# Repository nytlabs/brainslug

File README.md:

brainslug
=========

Brainslug is the internal name for a wearable we're experimenting with - this is the board that powers it. It combines an RFduino (ARM Cortex + BLE stack) and some MOSFET drivers to actuate high-current peripherals (heat pad, super-bright LED, peltier junction, etc).

Eagle board files for a small RFD22301 shield

This board allows an RFD22301 unit to address a dual-channel N-MOSFET IC on pins 0 and 1.

BOM:

(1) MOSFET IC http://www.digikey.com/product-detail/en/FDS6911/FDS6911CT-ND/1197695

(1) 3V3 regulator https://www.sparkfun.com/products/11253

(1) RFD22301 http://www.semiconductorstore.com/cart/pc/viewPrd.asp?idproduct=48872

(1) 10uF 0805 cap https://www.sparkfun.com/products/11244 (not strictly necessary, but wise)

...the board is laid out to use SMD JST connectors (https://www.sparkfun.com/products/8612) for battery and two loads, but you can also solder your own connectiors

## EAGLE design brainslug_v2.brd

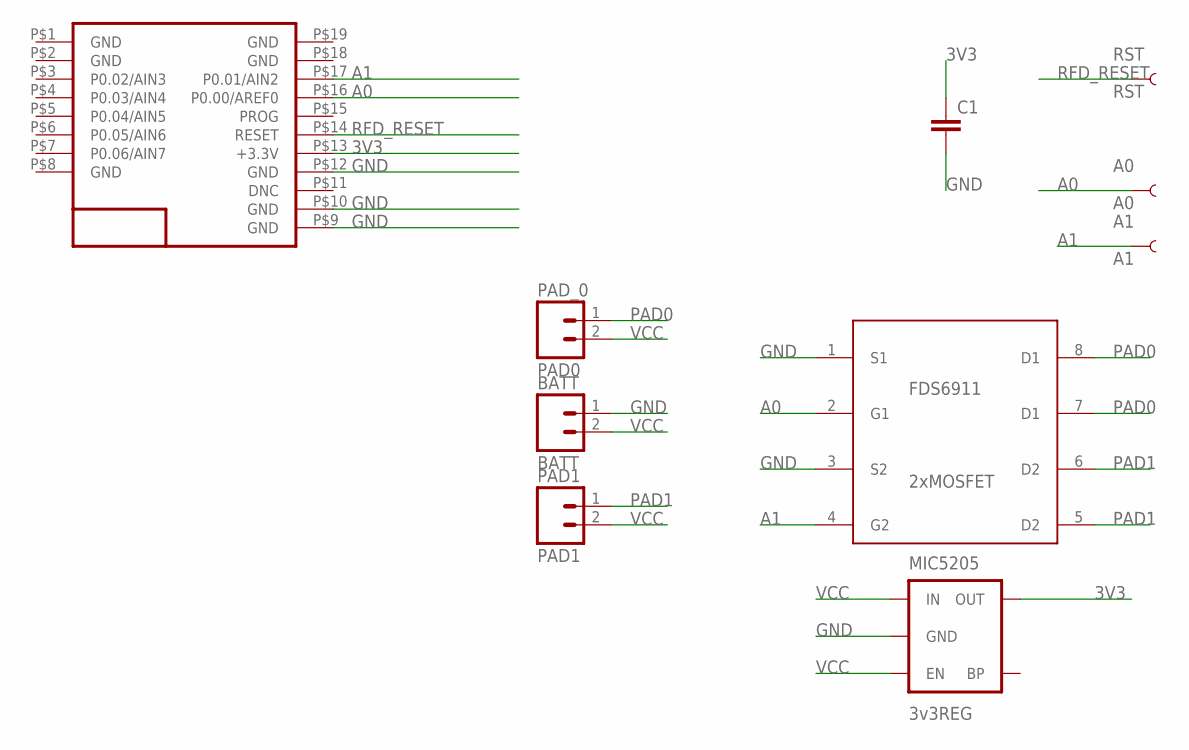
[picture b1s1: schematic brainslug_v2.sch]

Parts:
A0: A0; PAD.03X.03
A1: A1; PAD.03X.03
BATT: BATT; JST-2-SMD
C1: CAP; C3216
FDS6911: 2xMOSFET; SO8
MIC5205: 3v3REG; SOT23-5
PAD1: PAD1; JST-2-SMD
PAD_0: PAD0; JST-2-SMD
RST: RST; PAD.03X.03
U$1: RFD22301; RFD21733

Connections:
3V3: C1.1, MIC5205.5 (OUT), U$1.P$13 (+3.3V)
A0: A0.P$1, FDS6911.2 (G1), U$1.P$16 (P0.00/AREF0)
A1: A1.P$1, FDS6911.4 (G2), U$1.P$17 (P0.01/AIN2)
GND: BATT.1 (2), C1.2, FDS6911.1 (S1), FDS6911.3 (S2), MIC5205.2 (GND), U$1.P$9 (GND), U$1.P$10 (GND), U$1.P$12 (GND)
PAD0: FDS6911.7 (D1), FDS6911.8 (D1), PAD_0.1 (2)
PAD1: FDS6911.5 (D2), FDS6911.6 (D2), PAD1.1 (2)
RFD_RESET: RST.P$1, U$1.P$14 (RESET)
VCC: BATT.2 (1), MIC5205.1 (IN), MIC5205.3 (EN), PAD1.2 (1), PAD_0.2 (1)

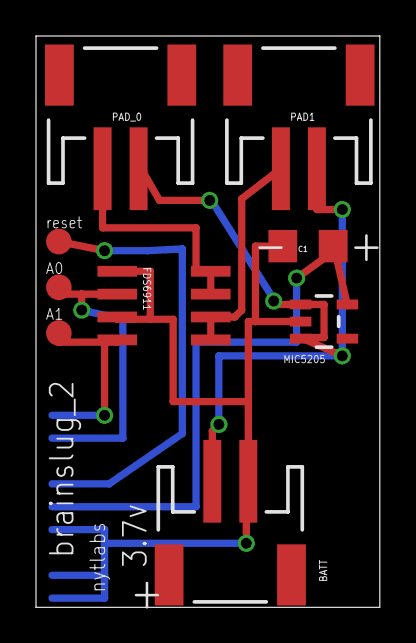
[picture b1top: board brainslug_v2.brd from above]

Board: 2 copper layers, 19.1 x 31.7 mm, 10 parts (1 on the bottom side), 8 nets.

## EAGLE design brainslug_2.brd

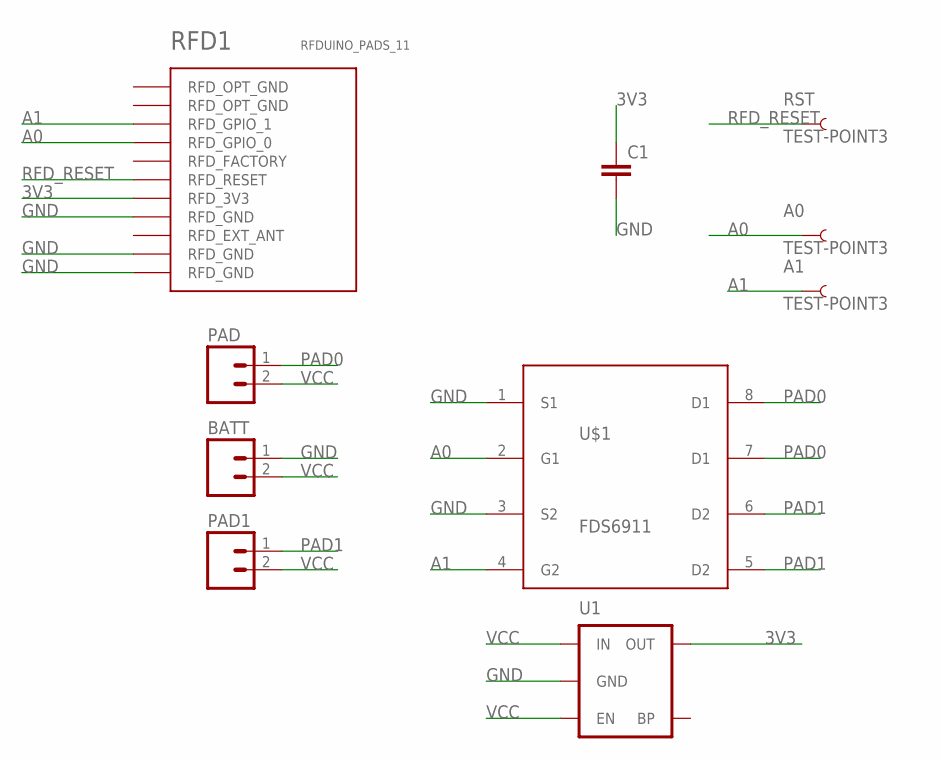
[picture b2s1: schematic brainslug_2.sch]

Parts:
A0, A1: TEST-POINT3; PAD.03X.03
BATT: M02-JST-2MM-SMT; JST-2-SMD
C1: CAP; C3216
PAD, PAD1: M02-JST-2MM-SMT; JST-2-SMD
RFD1: RFDUINO_PADS_11; RFDUINO_PADS
RST: TEST-POINT3; PAD.03X.03
U1: MIC52053.3V; SOT23-5
U$1: FDS6911; SO8

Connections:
3V3: C1.1, RFD1.RFD_3V3, U1.5 (OUT)
A0: A0.P$1, RFD1.RFD_GPIO_0, U$1.2 (G1)
A1: A1.P$1, RFD1.RFD_GPIO_1, U$1.4 (G2)
GND: BATT.1 (2), C1.2, RFD1.RFD_GND@0 (RFD_GND), RFD1.RFD_GND@1 (RFD_GND), RFD1.RFD_GND@2 (RFD_GND), U1.2 (GND), U$1.1 (S1), U$1.3 (S2)
PAD0: PAD.1 (2), U$1.7 (D1), U$1.8 (D1)
PAD1: PAD1.1 (2), U$1.5 (D2), U$1.6 (D2)
RFD_RESET: RFD1.RFD_RESET, RST.P$1
VCC: BATT.2 (1), PAD.2 (1), PAD1.2 (1), U1.1 (IN), U1.3 (EN)

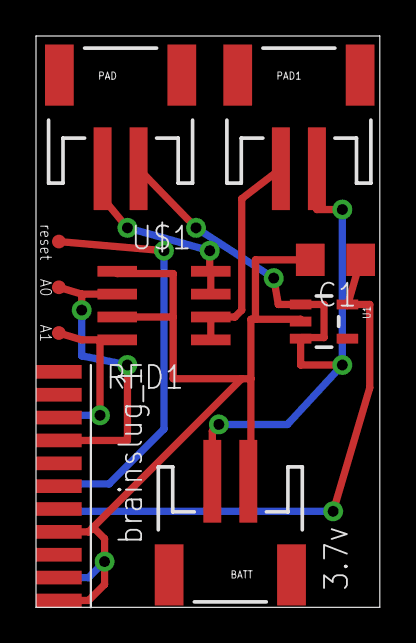
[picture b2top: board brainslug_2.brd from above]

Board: 2 copper layers, 19.1 x 31.7 mm, 10 parts (0 on the bottom side), 8 nets.

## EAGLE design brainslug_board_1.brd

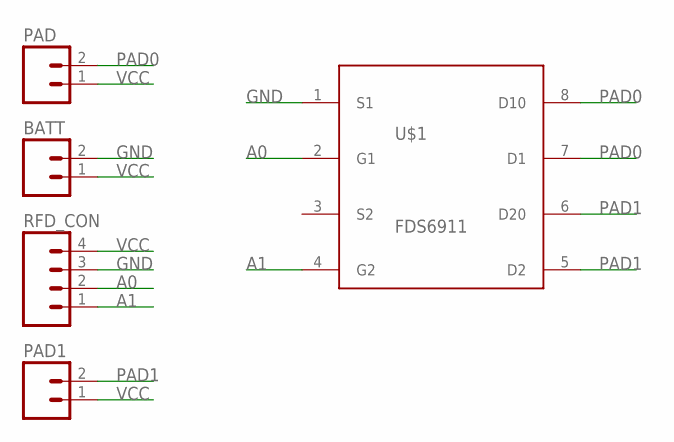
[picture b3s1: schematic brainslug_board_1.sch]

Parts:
BATT: M02PTH; 1X02
PAD, PAD1: M02PTH; 1X02
RFD_CON: M04PTH; 1X04
U$1: FDS6911; SO8

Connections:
A0: RFD_CON.2, U$1.2 (G1)
A1: RFD_CON.1, U$1.4 (G2)
GND: BATT.2, RFD_CON.3, U$1.1 (S1)
PAD0: PAD.2, U$1.7 (D1), U$1.8 (D10)
PAD1: PAD1.2, U$1.5 (D2), U$1.6 (D20)
VCC: BATT.1, PAD.1, PAD1.1, RFD_CON.4

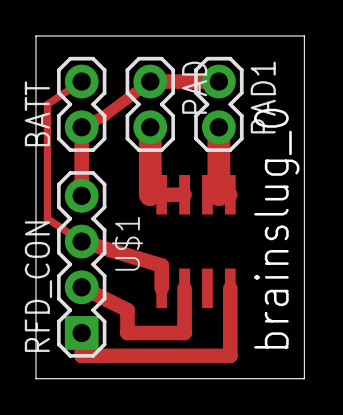
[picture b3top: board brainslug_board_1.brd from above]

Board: 2 copper layers, 15.0 x 19.0 mm, 5 parts (0 on the bottom side), 6 nets.

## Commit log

2014-01-17 cleaning up unusable first iterations of board - v5 is the first stable version
2014-01-17 Formatting fixes for README.md
2014-03-25 added more robust programming header, some other small improvements
2014-04-03 cleanup

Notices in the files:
parts and their libraries:
SparkFun-Connectors: Licensing: CC v3.0 Share-Alike You are welcome to use this library for commercial purposes.
